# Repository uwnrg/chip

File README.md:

# C.H.I.P.

This is a repository for the Conductive Hydrodynamic Ink Printer (CHIP), our current fabrication robot. It is an additive manufacturing device that uses conductive, water-based nanoparticle inks to create circuits and sensors for a variety of applications. This robot allows us to explore applications in PCB fabrication, integrated devices, wearable sensors, and printed displays. Our aim with this platform is to broaden our robot development capabilities by adding a new fabrication technique to our team.

---

## Folder Structure

### 1. `controls`

**Purpose:**
The `controls` folder contains the code responsible for moving the robotic components in the device. This includes scripts and configurations that enable precise motion and control of the robotic elements.

**Contents:**

- Scripts for motor control and coordination.
- Configuration files for tuning robotic movement.
- Documentation related to control algorithms and parameters.

**Usage:**

1. Develop and test motion control algorithms in this folder.
2. Update configuration files to match the specific hardware setup.
3. Ensure proper documentation of control logic for maintainability.

### 2. `mechanical`

**Purpose:**
The `mechanical` folder contains all files and designs related to the mechanical aspects of the device. This includes the framing, fasteners, motor holders, threaded rod catchers, and other structural components.

**Contents:**

- `single_parts/`: Contains designs for individual components.
- `assemblies/`: Contains complete assemblies composed of multiple parts.
- CAD files, schematics, and design documentation.

**Usage:**

1. Store individual part designs in the `single_parts/` subfolder.
2. Save assembly designs in the `assemblies/` subfolder.
3. Update design documentation to reflect any changes to parts or assemblies.

### 3. `electronics`

**Purpose:**
The `electronics` folder is dedicated to the electronic components of the device. It includes diagrams, part lists, 3d models, and other resources needed for the electronic systems.

**Contents:**

- Circuit diagrams and schematics.
- Bill of materials (BOM) for electronic parts.
- Datasheets and reference materials for components.
- Documentation related to the electronic side of things

**Usage:**

1. Add circuit diagrams and schematics for the project.
2. Document electronic components in a structured BOM.
3. Store relevant datasheets and reference materials for easy access.
4. Any related documentation for this system's electronics

---

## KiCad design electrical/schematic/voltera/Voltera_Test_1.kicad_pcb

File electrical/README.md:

# C.H.I.P. Electronics

This is the electronics side of the CHIP project. This includes the circuit related components, such as pcb and cad designs. Firmware is found in the `controls` folder back in the main directory.

---

## Folder Structure

### 1. `cad_design`

**Purpose:**
The `cad_design` folder contains CAD files related to the circuity. This mainly includes housing for these circuits.

**Contents:**

- Solidwork files for PSU
- PCB box files

**Usage:**

1. Any CAD files should be placed here
2. 3D printing files, like GCODE can also go here

### 2. `documentation`

**Purpose:**
The `documentation` folder contains documentation on the entire design process for the electronic side of things.

**Contents:**

- Documentation on processes
- Images of said processes

**Usage:**

1. Store important information on the workings of the fabrication process
2. Any information on recreating the project

### 3. `schematic`

**Purpose:**
The `schematic` folder is dedicated to the electronic schematics for PCB design.

**Contents:**

- Circuit diagrams and schematics.
- Datasheets and reference materials for components.

**Usage:**

1. Add circuit diagrams and schematics for the project.
2. Store relevant datasheets and reference materials for easy access.

---

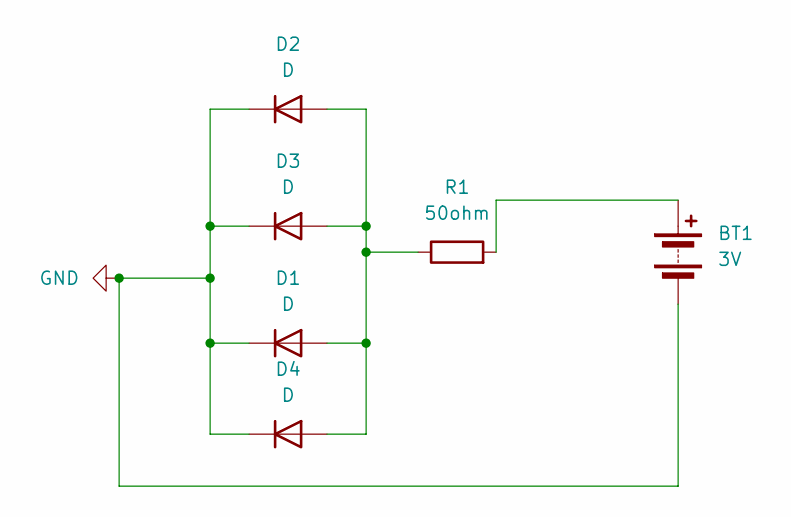
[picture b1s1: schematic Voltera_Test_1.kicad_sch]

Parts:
BT1: 3V; PinHeader_1x02_P1.00mm_Vertical
D1, D2: D; D_0402_1005Metric
D3, D4: D; D_DO-15_P3.81mm_Vertical_KathodeUp
R1: 50ohm; R_Axial_DIN0204_L3.6mm_D1.6mm_P5.08mm_Horizontal

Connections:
GND: BT1.2 (-), D1.1 (K), D2.1 (K), D3.1 (K), D4.1 (K)
unnamed: BT1.1 (+), R1.2
unnamed: D1.2 (A), D2.2 (A), D3.2 (A), D4.2 (A), R1.1

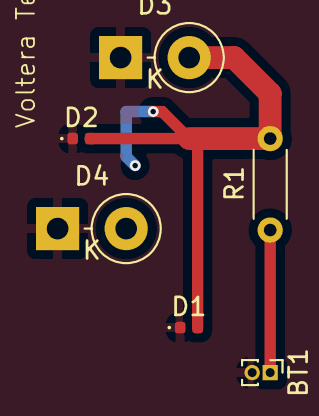
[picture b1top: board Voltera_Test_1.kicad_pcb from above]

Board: 2 copper layers, 6 parts (0 on the bottom side), 3 nets.

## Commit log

2025-01-30 initialize mechanical directory
2025-01-30 initialize electrical and controls
2025-02-17 Add files via upload
    Electrical Schematic for CHIP based on RAMPS 4.1
2025-02-20 extract schematic files
2025-02-28 Add files via upload
    Updated motor holder to have right hole sizes for linear rods. Adjusted distance between linear rods to match x-axis baseplate rod guides and threaded rod catcher
2025-03-02 Create the marlin folder
2025-03-02 Delete controls/marlin
    Wasn't a folder so had to delete
2025-03-02 Create README.md for Marlin
    Ok now it is a folder 👍
2025-03-02 Revert "Create README.md for Marlin"
2025-03-02 Update README.md
    Added information about the configuration files.
2025-03-02 Uploading marlin config files
2025-03-25 Create PCB Box
2025-04-01 Update Configuration.h
    modified to fix compilation errors
2025-04-04 re-organize repo; add haya/gaby stuff
2025-04-04 adding discord images
2025-04-12 adding Dany's stuff
2025-05-14 Create Fluid Deposition
2025-07-18 Add files via upload
    simple traces to test x and y motors
